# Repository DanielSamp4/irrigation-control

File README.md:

# Control plants irrigation using ESP32

A challenge made by Neurobots

# Overview

This project consist in creat a system that can irrigate plants based on day period and degree of humidity. This system have to be pownred by a battery of 3.7v 

### System

<div align="center">

 In summary, the system is made to charge the battery with solar pannels or power grid (giving priority to the power grid), and power a ESP32 that will be the brain operation, that will check if LDR and Soil Hmidity Sensor get in determinate condition, and will trigger the circuit switch to activate the solenoid, therefore irrigating a plant.

 The Soil Hmidity Sensor, Solenoid and LDR have conectors attached to the PCB (See Hardware Section) to connect them, and the user feel free to use them.
 
### Power Circuit
lithium batteries can be dangerous if not charged properly and that's why the TP4056 is useful as it stops over voltage and current charging by detecting specific voltage conditions. You should never use the TP4056 as a charger and as a load driver at the same time. For this we will use a PMOSFET that will function like a controlled switch that disconnects the battery when external power is applied. The TP4056 still charges the battery but without a load. Power to the load is supplied from the power source directly.

To know more about the right way to use TP4056 see https://www.best-microcontroller-projects.com/tp4056.html

### Logical Circuit

Both LDR and Sensor Humidity are analog devices, therefore can be atached to any ADC GPIO of ESP32, i choose GPIO 34 and 35 (See Firmware Section).

For Activate the solenoid, must be a output GPIO (anyone except 34, 35, 36, 39 because they are input only) and the circuit switch will be a NMOSFET with gate connect to GPIO, drain connect to GND from the solenoid and source connect to GND from the circuit, with this configuration when GPIO is high the NMOSFET will connect the GND from NMOSFET with the GND from de circuit and de valvula solenoid will open. I will connect to GPIO 25 and will use PWM signal to see if will genarate some kind of water flow control from solenoid.

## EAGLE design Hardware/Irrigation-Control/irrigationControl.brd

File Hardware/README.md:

# Hardware

### Schematic
<div align="center">

<div align="center">

<div align="center">

### Board
<div align="center">

### Manufactoring
<div align="center">

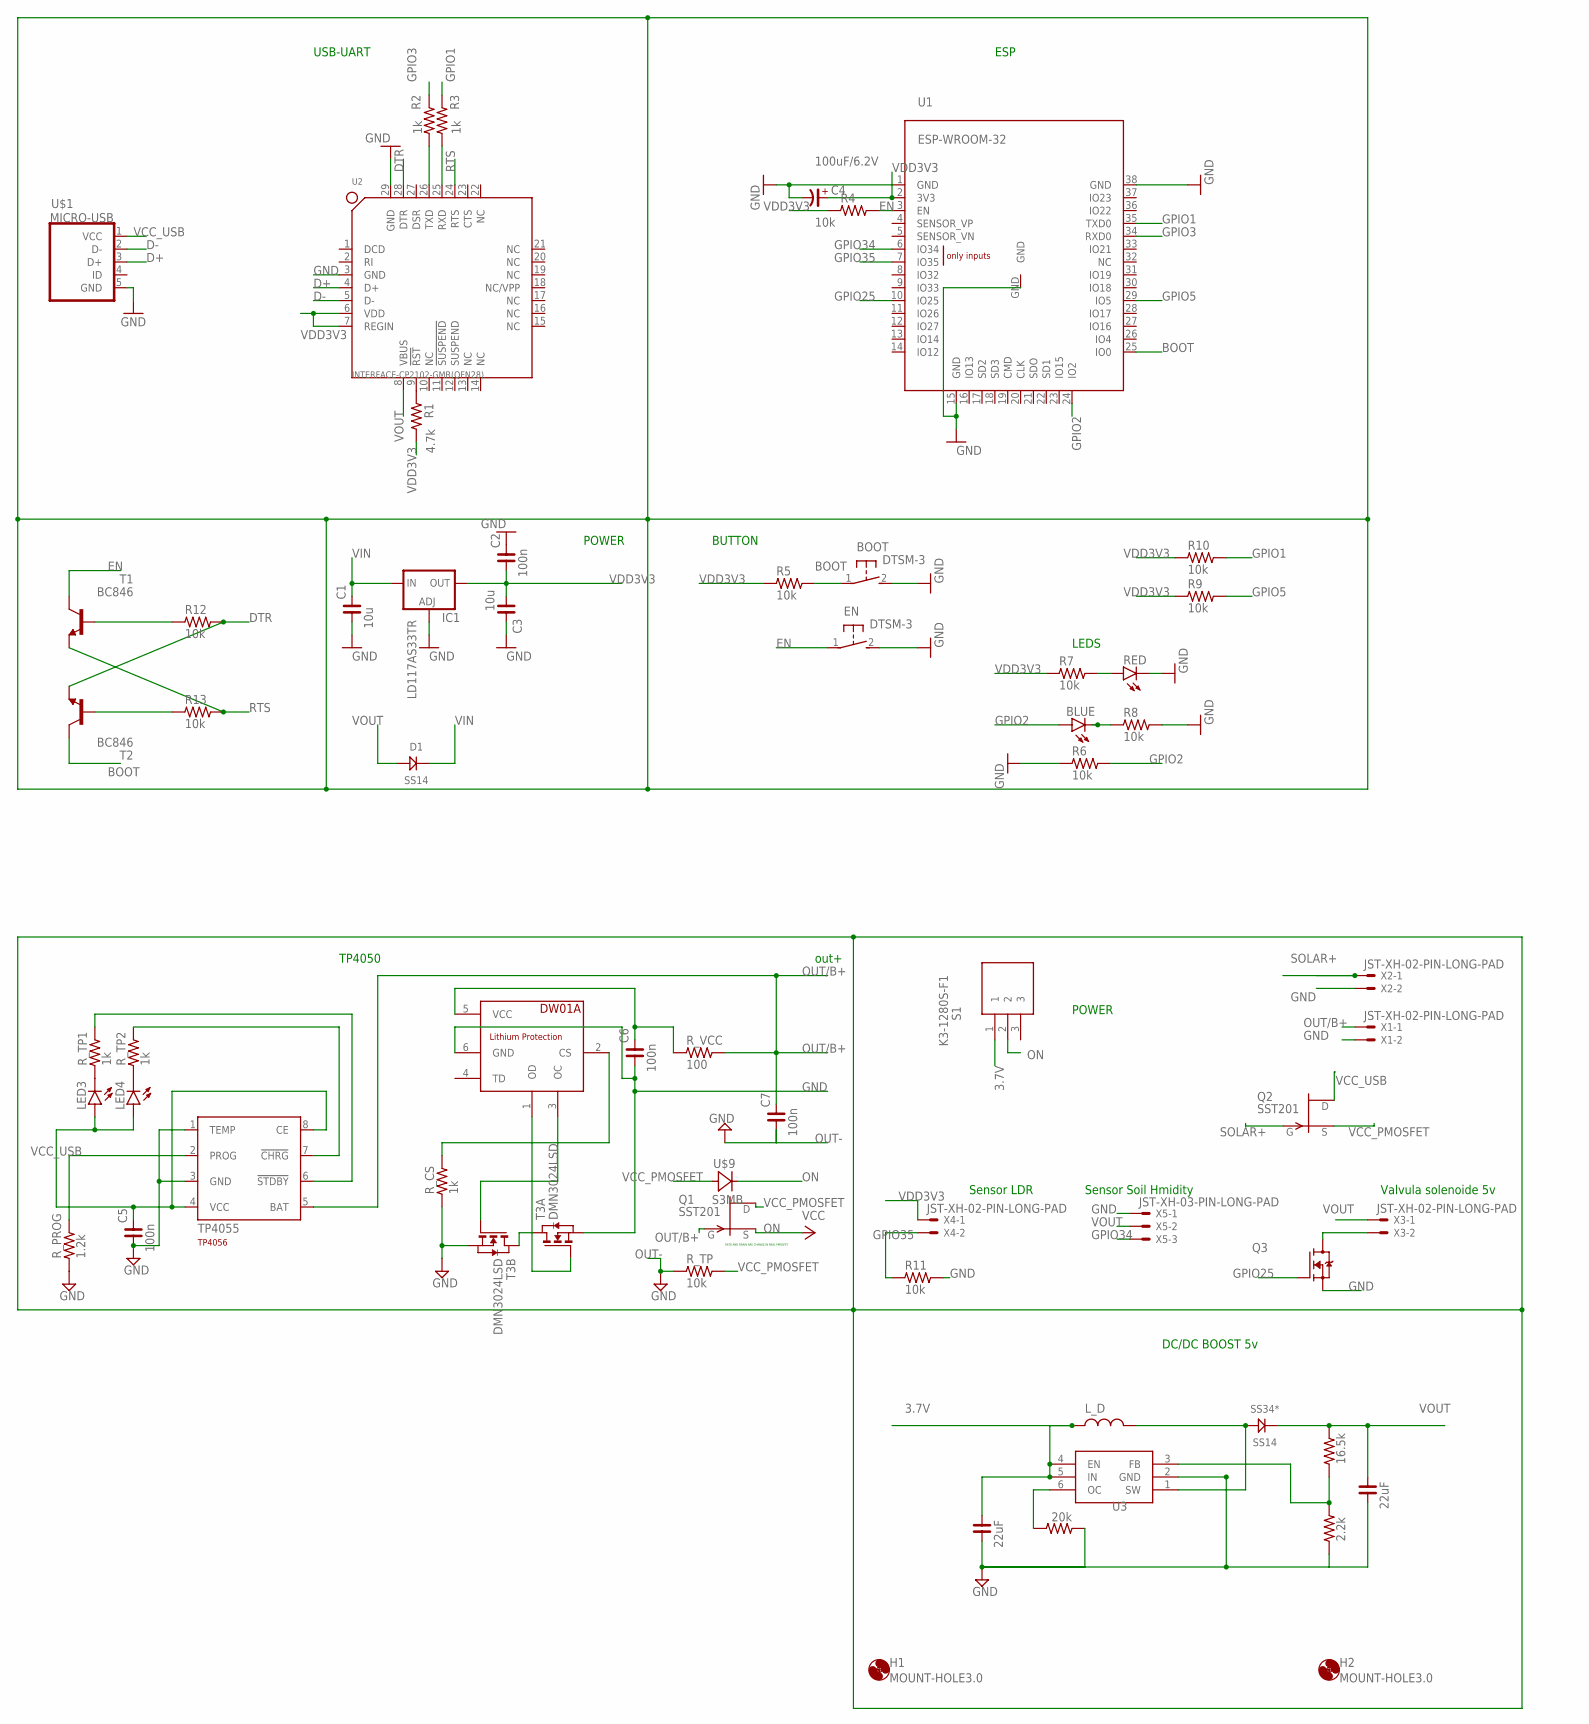
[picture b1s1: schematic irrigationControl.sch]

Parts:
BLUE: blue; CHIPLED_0603
BOOT: DTSM-3
C1, C3: 10u; C0603
C1BOOST, C2BOOST: 22uF; C1206
C2, C5, C6, C7: 100n; C0603
C4: 100uF/6.2V; C3216-18/T
D1: SS14; DO214
DW01A: DW01A; SOT23-6
EN: DTSM-3
H1, H2: MOUNT-HOLE3.0; 3,0
IC1: LD117AS33TR; SOT223
LED3, LED4: LED3MM
L_D: SLW6045S221MST
Q1, Q2: SST201; SOT23
Q3: TRANSISTOR_FET_BS170-SOT-23; SOT-23
R1: 4.7k; R0603
R2, R3: 1k; R0603
R4, R5, R6, R7, R8, R9, R10, R11, R12, R13: 10k; R0603
RED: red; CHIPLED_0603
RESISTOR1BOOST: 16.5k; R0603
RESISTOR1BOOST2: 2.2k; R0603
RESISTOR1BOOST3: 20k; R0603
R_CS: 1k; R0603
R_PROG: 1.2k; R0603
R_TP: 10k; R0603
R_TP1, R_TP2: 1k; R0603
R_VCC: 100; R0603
S1: K3-1280S-F1; K31280SF1
SS34*: SS14; DO214
T1, T2: BC846; SOT23
T3: DMN3024LSD; TSSOP-8
TP4055: TP4056; SOT23-8
U1: ESP-WROOM-32
U2: INTERFACE-CP2102-GMR(QFN28); QFN28G_0.5-5X5MM
U3: MT3608; SOT95P280X145-6N
U$1: MICRO-USB; MICRO-USB-2
U$9: S3MB
X1, X2, X3, X4: JST-XH-02-PIN-LONG-PAD; JST-XH-02-PACKAGE-LONG-PAD
X5: JST-XH-03-PIN-LONG-PAD; JST-XH-03-PACKAGE-LONG-PAD

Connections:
3.7V: C1BOOST.2, L_D.1, S1.1, U3.4 (EN), U3.5 (IN)
BOOT: BOOT.1, R5.2, T2.3 (C), U1.25 (IO0)
D+: U2.4 (D+), U$1.3 (D+)
D-: U2.5 (D-), U$1.2 (D-)
DTR: R12.2, T2.2 (E), U2.28 (DTR)
EN: EN.1, R4.2, T1.3 (C), U1.3 (EN)
GND: BOOT.2, C1.1, C1BOOST.1, C2.2, C2BOOST.1, C3.2, C4.-, C5.1, C6.1, DW01A.6 (GND), EN.2, IC1.1 (ADJ), Q3.2 (S), R6.1, R8.2, R11.2, RED.C, RESISTOR1BOOST2.1, RESISTOR1BOOST3.1, R_CS.1, R_PROG.1, T3.2 (S), T3.3 (S), T3.6 (S), T3.7 (S), TP4055.1 (TEMP), TP4055.3 (GND), U1.1 (GND), U1.15 (GND), U1.38 (GND), U1.GND, U2.3 (GND), U2.29 (GND), U3.2 (GND), U$1.5 (GND), X1.2, X2.2, X5.1
GPIO1: R3.1, R10.2, U1.35 (TXD0)
GPIO2: BLUE.A, R6.2, U1.24 (IO2)
GPIO3: R2.1, U1.34 (RXD0)
GPIO5: R9.2, U1.29 (IO5)
GPIO25: Q3.1 (G), U1.10 (IO25)
GPIO34: U1.6 (IO34), X5.3
GPIO35: R11.1, U1.7 (IO35), X4.2
unnamed: R1.1, U2.9 (!RST)
unnamed: R2.2, U2.26 (TXD)
unnamed: R3.2, U2.25 (RXD)
unnamed: R12.1, T1.1 (B)
unnamed: R13.1, T2.1 (B)
unnamed: BLUE.C, R8.1
unnamed: Q3.3 (D), X3.2
unnamed: L_D.2, SS34*.ANODE, U3.1 (SW)
unnamed: RESISTOR1BOOST.1, RESISTOR1BOOST2.2, U3.3 (FB)
unnamed: RESISTOR1BOOST3.2, U3.6 (OC)
unnamed: LED3.K (C), R_TP1.1
unnamed: LED4.K (C), R_TP2.1
unnamed: R7.2, RED.A
unnamed: R_TP2.2, TP4055.7 (!CHRG)
unnamed: R_TP1.2, TP4055.6 (!STDBY)
unnamed: R_PROG.2, TP4055.2 (PROG)
unnamed: T3.1 (D), T3.8 (D)
unnamed: DW01A.3 (OC), T3.5 (G)
unnamed: DW01A.2 (CS), R_CS.2
unnamed: DW01A.1 (OD), T3.4 (G)
unnamed: C6.2, DW01A.5 (VCC), R_VCC.1
ON: Q1.2 (S), S1.2, U$9.-
OUT-: C7.1, R_TP.1
OUT/B+: C7.2, Q1.3 (G), R_VCC.2, TP4055.5 (BAT), X1.1
RTS: R13.2, T1.2 (E), U2.24 (RTS)
SOLAR+: Q2.3 (G), X2.1
VCC_PMOSFET: Q1.1 (D), Q2.2 (S), R_TP.2, U$9.+
VCC_USB: C5.2, LED3.A, LED4.A, Q2.1 (D), TP4055.4 (VCC), TP4055.8 (CE), U$1.1 (VCC)
VDD3V3: C2.1, C3.1, C4.+, IC1.4 (OUT), R1.2, R4.1, R5.1, R7.1, R9.1, R10.1, U1.2 (3V3), U2.6 (VDD), U2.7 (REGIN), X4.1
VIN: C1.2, D1.CATHODE (KATHODE), IC1.3 (IN)
VOUT: C2BOOST.2, D1.ANODE, RESISTOR1BOOST.2, SS34*.CATHODE (KATHODE), U2.8 (VBUS), X3.1, X5.2

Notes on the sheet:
POWER
ESP
USB-UART
BUTTON
LEDS
GATE AND DRAIN ARE CHANGE IN REAL PMOSFET
TP4050
out+
DC/DC BOOST 5v
Sensor LDR
Sensor Soil Hmidity
Valvula solenoide 5v

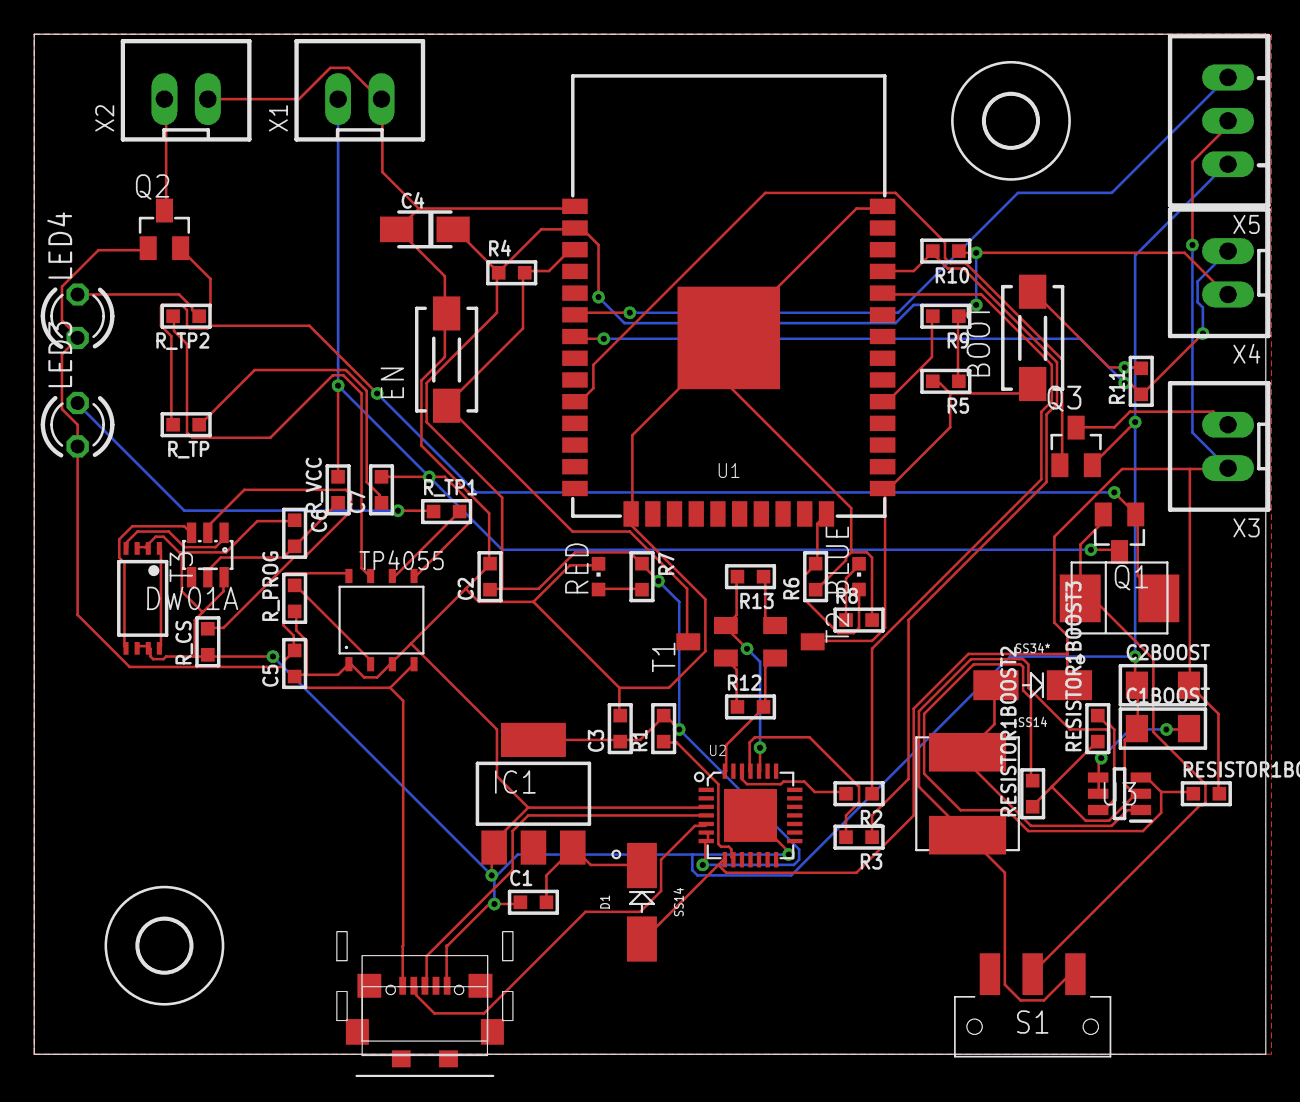
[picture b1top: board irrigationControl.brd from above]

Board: 2 copper layers, 72.1 x 59.7 mm, 62 parts (0 on the bottom side), 45 nets.

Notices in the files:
parts and their libraries:
rc-master-smd: Copyright (C) 2007, Bob Starr
